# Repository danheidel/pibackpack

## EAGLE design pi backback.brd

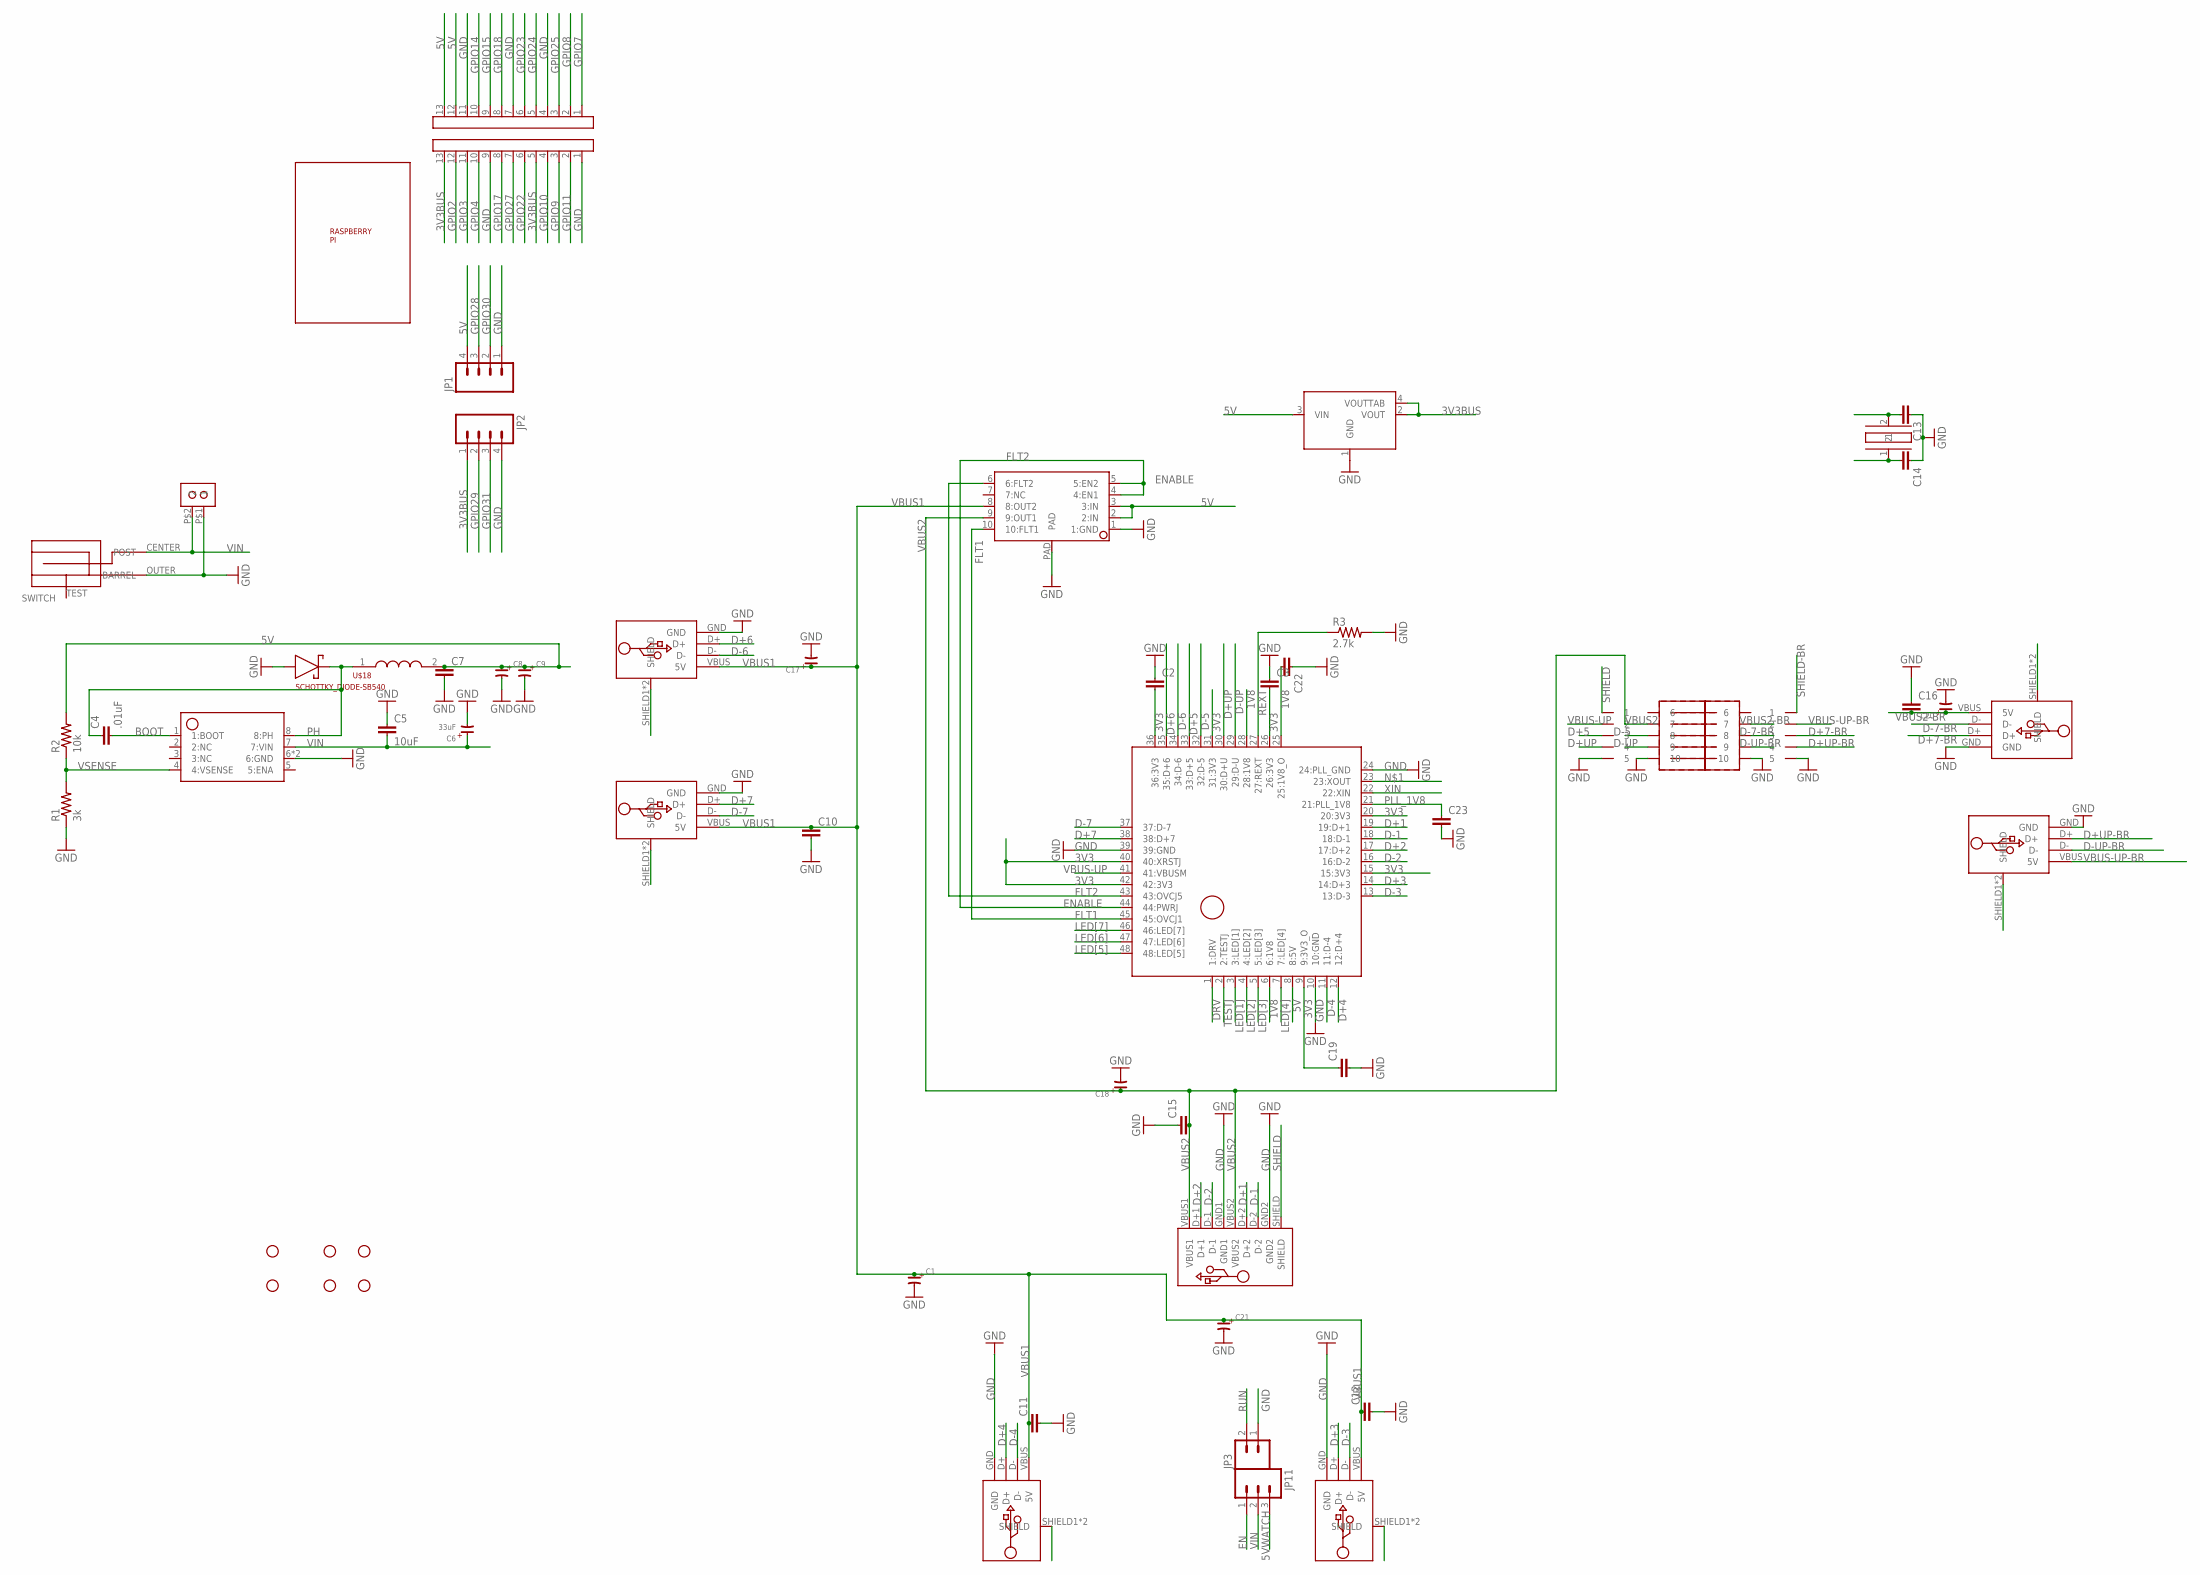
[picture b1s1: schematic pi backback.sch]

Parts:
C1, C17, C18, C20, C21: CAPPOL-5X11; 5X11MMCAP
C2, C3, C10, C11, C12, C15, C16, C23: CAP0805; 0805
C4: .01uF; 0603-CAP
C5: 10uF; 1206
C6: 33uF; 8MMCAP
C7, C19, C22: CAP1206; 1206
C8, C9: CAPPOL-XX6.3; 6.3MMDIAMELECTROLYTIC
C13, C14: CAP0603-CAP; 0603-CAP
JP1, JP2: M04LOCK; 1X04_LOCK
JP3: M02LOCK; 1X02_LOCK
JP4, JP5, JP6, JP7, JP9, JP10: STAND-OFFTIGHT; STAND-OFF-TIGHT
JP11: M03LOCK; 1X03_LOCK
R1: 3k; 0805
R2: 10k; 0805
R3: 2.7k; 0805
U$1: RASPBERRY-PI-OUTLINE; RASPBERRY-PI-REV2-OUTLINE
U$2, U$3: M13; 1X13_LOCK
U$4: TPS200(2/3)C; SON-10
U$5: FE2.1-48; LQFP-48
U$6: USB-A-MALE
U$7: SCREWTERM-2MA212-2; MA212-2
U$8, U$9, U$10, U$12, U$16: USB-A-FEMALE
U$11: USB_HEADER
U$13: TPS5450; SOIC8-POWERPAD
U$14: M05X02_FEM-LOCK_RIGHT_ANGLE_FEM; 2X05_LOCK_RIGHT_ANGLE_FEM
U$15: M05X02_MALE; 2X05_LOCK_RIGHT_ANGLE_MALE
U$17: POWER-JACK-2.1MM; 2.1MM-POWER-JACK
U$18: INDUCTOR-DR13-RT-A; DR13-RT-A
U$19: SCHOTTKY_DIODE-SB540; DO-201-AD
U$20: CRYSTAL-HC49; HC49US
U$21: 3V3-LDO-ZLDO1117; ZLDO1117

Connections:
1V8: C22.2, U$5.6 (6:1V8), U$5.25 (25:1V8_O), U$5.28 (28:1V8)
3V3: C2.2, C3.2, C19.1, U$5.9 (9:3V3_O), U$5.15 (15:3V3), U$5.20 (20:3V3), U$5.26 (26:3V3), U$5.31 (31:3V3), U$5.36 (36:3V3), U$5.40 (40:XRSTJ), U$5.42 (42:3V3)
3V3BUS: JP2.1, U$2.5, U$2.13, U$21.2 (VOUT), U$21.4 (VOUTTAB)
5V: C7.1, C8.+, C9.+, JP1.4, R2.2, U$3.12, U$3.13, U$4.2 (2:IN), U$4.3 (3:IN), U$5.8 (8:5V), U$18.2, U$21.3 (VIN)
5VWATCH: JP11.3
BOOT: C4.2, U$13.1 (1:BOOT)
D+1: U$5.19 (19:D+1), U$11.D+2
D+2: U$5.17 (17:D+2), U$11.D+1
D+3: U$5.14 (14:D+3), U$12.D+
D+4: U$5.12 (12:D+4), U$16.D+
D+5: U$5.33 (33:D+5), U$14.3
D+6: U$5.35 (35:D+6), U$9.D+
D+7: U$5.38 (38:D+7), U$8.D+
D+7-BR: U$10.D+, U$15.3
D+UP: U$5.30 (30:D+U), U$14.4
D+UP-BR: U$6.D+, U$15.4
D-1: U$5.18 (18:D-1), U$11.D-2
D-2: U$5.16 (16:D-2), U$11.D-1
D-3: U$5.13 (13:D-3), U$12.D-
D-4: U$5.11 (11:D-4), U$16.D-
D-5: U$5.32 (32:D-5), U$14.8
D-6: U$5.34 (34:D-6), U$9.D-
D-7: U$5.37 (37:D-7), U$8.D-
D-7-BR: U$10.D-, U$15.8
D-UP: U$5.29 (29:D-U), U$14.9
D-UP-BR: U$6.D-, U$15.9
DRV: U$5.1 (1:DRV)
EN: JP11.1
ENABLE: U$4.4 (4:EN1), U$4.5 (5:EN2), U$5.44 (44:PWRJ)
FLT1: U$4.10 (10:FLT1), U$5.45 (45:OVCJ1)
FLT2: U$4.6 (6:FLT2), U$5.43 (43:OVCJ5)
GND: C1.-, C2.1, C3.1, C5.1, C6.-, C7.2, C8.-, C9.-, C10.2, C11.2, C12.2, C13.1, C14.1, C15.1, C16.1, C17.-, C18.-, C19.2, C20.-, C21.-, C22.1, C23.2, JP1.1, JP2.4, JP3.1, R1.1, R3.2, U$2.1, U$2.9, U$3.4, U$3.7, U$3.11, U$4.1 (1:GND), U$4.PAD, U$5.10 (10:GND), U$5.24 (24:PLL_GND), U$5.39 (39:GND), U$6.GND, U$7.P$1 (1), U$8.GND, U$9.GND, U$10.GND, U$11.GND1, U$11.GND2, U$12.GND, U$13.6 (6:GND), U$13.PAD (6:GND), U$14.5, U$14.10, U$15.5, U$15.10, U$16.GND, U$17.OUTER (BARREL), U$19.A (ANODE), U$21.1 (GND)
GPIO2: U$2.12
GPIO3: U$2.11
GPIO4: U$2.10
GPIO7: U$3.1
GPIO8: U$3.2
GPIO9: U$2.3
GPIO10: U$2.4
GPIO11: U$2.2
GPIO14: U$3.10
GPIO15: U$3.9
GPIO17: U$2.8
GPIO18: U$3.8
GPIO22: U$2.6
GPIO23: U$3.6
GPIO24: U$3.5
GPIO25: U$3.3
GPIO27: U$2.7
GPIO28: JP1.3
GPIO29: JP2.2
GPIO30: JP1.2
GPIO31: JP2.3
LED[1]: U$5.3 (3:LED[1])
LED[2]: U$5.4 (4:LED[2])
LED[3]: U$5.5 (5:LED[3])
LED[4]: U$5.7 (7:LED[4])
LED[5]: U$5.48 (48:LED[5])
LED[6]: U$5.47 (47:LED[6])
LED[7]: U$5.46 (46:LED[7])
unnamed: C14.2, U$20.1
PH: C4.1, U$13.8 (8:PH), U$18.1, U$19.C (CATHODE)
PLL_1V8: C23.1, U$5.21 (21:PLL_1V8)
REXT: R3.1, U$5.27 (27:REXT)
RUN: JP3.2
SHIELD: U$8.SHIELD1 (SHIELD), U$8.SHIELD2 (SHIELD), U$9.SHIELD1 (SHIELD), U$9.SHIELD2 (SHIELD), U$11.SHIELD, U$12.SHIELD1 (SHIELD), U$12.SHIELD2 (SHIELD), U$14.1, U$16.SHIELD1 (SHIELD), U$16.SHIELD2 (SHIELD)
SHIELD-BR: U$6.SHIELD1 (SHIELD), U$6.SHIELD2 (SHIELD), U$10.SHIELD1 (SHIELD), U$10.SHIELD2 (SHIELD), U$15.1
TESTJ: U$5.2 (2:TESTJ)
VBUS1: C1.+, C10.1, C11.1, C12.1, C17.+, C21.+, U$4.8 (8:OUT2), U$8.VBUS (5V), U$9.VBUS (5V), U$12.VBUS (5V), U$16.VBUS (5V)
VBUS2: C15.2, C18.+, U$4.9 (9:OUT1), U$11.VBUS1, U$11.VBUS2, U$14.7
VBUS2-BR: C16.2, C20.+, U$10.VBUS (5V), U$15.7
VBUS-UP: U$5.41 (41:VBUSM), U$14.2
VBUS-UP-BR: U$6.VBUS (5V), U$15.2
VIN: C5.2, C6.+, JP11.2, U$7.P$2 (2), U$13.7 (7:VIN), U$17.CENTER (POST)
VSENSE: R1.2, R2.1, U$13.4 (4:VSENSE)
XIN: U$5.22 (22:XIN)
XOUT: C13.2, U$20.2

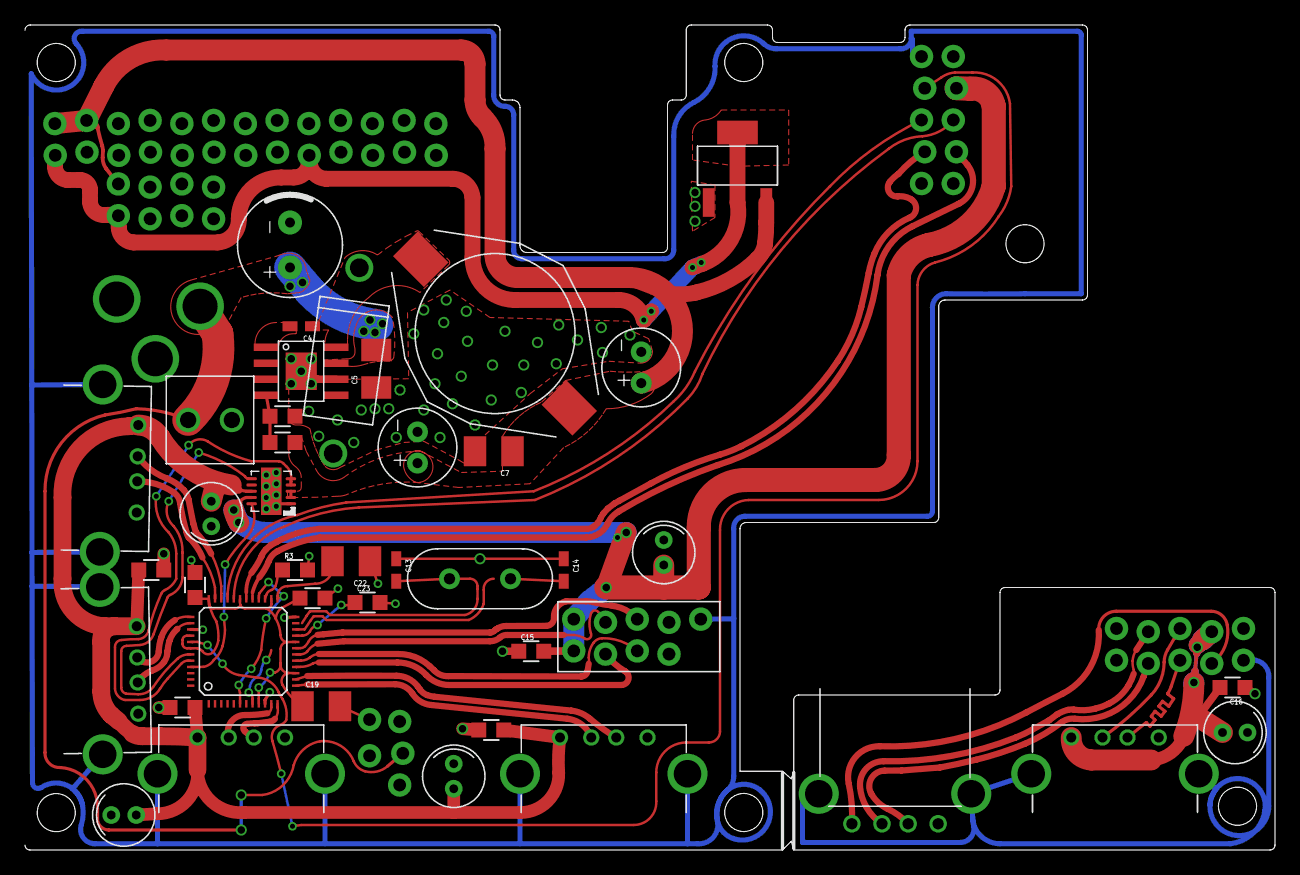
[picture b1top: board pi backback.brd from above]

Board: 2 copper layers, 100.0 x 66.0 mm, 57 parts (0 on the bottom side), 43 nets.
